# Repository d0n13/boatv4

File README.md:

# boatv4
2025 version of electric boat

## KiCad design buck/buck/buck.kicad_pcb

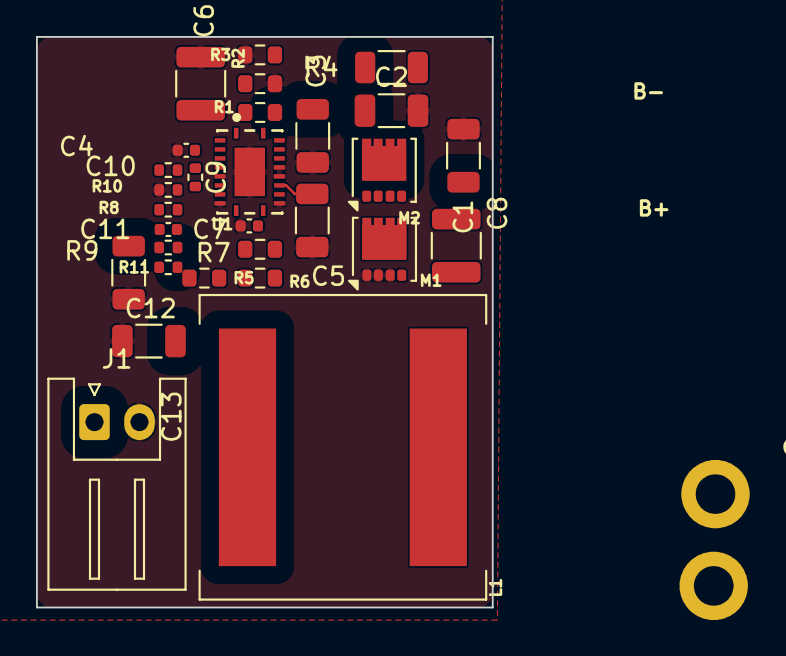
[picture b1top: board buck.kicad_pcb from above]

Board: 2 copper layers, 25.3 x 31.7 mm, 31 parts (0 on the bottom side), 19 nets.

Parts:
C1, C2, C3: 2.2uF x 3; C_1206_3216Metric
C4: 56nF; C_0402_1005Metric
C5: 2.2µF; C_1206_3216Metric
C6, C8: 100nF; C_1210_3225Metric
C7: 3pF; C_0402_1005Metric
C9: 8.2nF; R_0402_1005Metric
C10: 680pF; R_0402_1005Metric
C11: 560pF; C_0402_1005Metric
C12, C13: 22µF x 2; C_1206_3216Metric
H4, H5: MountingHole; MountingHole_2.2mm_M2_DIN965_Pad
J1: Conn_01x02_Socket; JST_XH_S2B-XH-A_1x02_P2.50mm_Horizontal
L1: 3µH; L_Coilcraft_XAL1580-302
M1, M2: CSD19537Q3; VSON-8_3.3x3.3mm_P0.65mm_NexFET
R1: 174kΩ; R_0603_1608Metric
R2: 7.68kΩ; R_0603_1608Metric
R3: 39.2kΩ; R_0603_1608Metric
R4: 2.1Ω; R_1206_3216Metric
R5, R6: 20kΩ; R_0603_1608Metric
R7: 1.96kΩ; R_0603_1608Metric
R8: 2.05kΩ; R_0402_1005Metric
R9: 18kΩ; R_0402_1005Metric
R10: 2.15kΩ; R_0402_1005Metric
R11: 66.5Ω; R_0402_1005Metric
U1: LM5146RGYR; RGY0020B-MFG

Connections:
+7.4V: C12.1, C13.1, J1.1, L1.1, R9.1, R11.1
+BATT: C1.1, C2.1, C3.1, M2.5 (D), R1.1, R4.1
GND: C1.2, C2.2, C3.2, C4.2, C5.2, C6.2, C7.2, C12.2, C13.2, J1.2, M1.1 (S), M1.2 (S), M1.3 (S), R2.2, R3.2, R10.2, U1.6 (AGND), U1.9 (NC), U1.12 (PGND), U1.15 (EP), U1.16 (NC), U1.21 (GND)
unnamed: C9.2, R8.1
unnamed: C11.1, R11.2
unnamed: C8.2, L1.2, M1.5 (D), M2.1 (S), M2.2 (S), M2.3 (S), R7.2, U1.19 (SW)
unnamed: M1.4 (G), U1.13 (LO)
unnamed: M2.4 (G), U1.18 (HO)
unnamed: C8.1, U1.17 (BST)
unnamed: C9.1, C10.1, U1.4 (COMP)
unnamed: R1.2, R2.1, U1.1 (EN_UVLO)
unnamed: C10.2, C11.2, R8.2, R9.2, R10.1, U1.5 (FB)
unnamed: C7.1, R7.1, U1.11 (ILIM)
unnamed: R6.2, U1.10 (PGOOD)
unnamed: R3.1, U1.2 (RT)
unnamed: C4.1, U1.3 (SS_TRK)
unnamed: R5.2, U1.8 (SYNCIN)
unnamed: C5.1, R5.1, R6.1, U1.14 (VCC)
unnamed: C6.1, R4.2, U1.20 (VIN)

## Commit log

2023-12-26 Added .gitignore
2023-12-26 Added source
2023-12-26 renamed
2023-12-26 deleted
2023-12-27 Set USB port to use
2023-12-27 Added files
2023-12-27 Updated for controls
2024-12-19 Added docs and buck design
2024-12-19 Change verison
2024-12-19 Added board QR Code
2024-12-19 PCB updates

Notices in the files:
buck/buck/buck.kicad_pcb:
© 2024 Donie Kelly
